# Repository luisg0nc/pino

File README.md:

<h1 align="center">pino</h1>

<p align="center">
  A desktop workbench for making circuit boards with an AI coding agent.<br>
  You point at the board. The agent writes the board in Python. pino builds it every time you save.
</p>

<p align="center">

</p>

<p align="center">
  <a href="https://pino.luisg.me/">pino.luisg.me</a> ·
  <a href="#getting-started">Getting started</a> ·
  <a href="#how-it-works">How it works</a> ·
  <a href="kernel/README.md">The engine</a> ·
  <a href="#contributing">Contributing</a>
</p>

> [!NOTE]
> pino is new and early. It is developed on Linux (Arch, Wayland), 100% using Claude Code, and runs on Linux only.
> Expect rough edges, and please [open an issue](https://github.com/luisg0nc/pino/issues) when you find one. Before
> you order a board, check every part in JLC's placement preview.

## Why pino

Coding agents can write a circuit board as code. Two things get in the way. The agent can't see the board it made,
and it's hard for you to tell it *which* track is wrong, or where a part should go. Pointing at a board is easy in
real life and slow to put into words.

pino fixes both. It runs [Claude Code](https://docs.anthropic.com/en/docs/claude-code) next to a live view of the
board, its schematic and a 3D model. You point at a part, draw an arrow to where it should go or sketch the way a
track should run, and the agent gets exactly what you pointed at: the part's reference, the pad, the net, your note.
The agent also gets tools to look at the board, measure it, read the checks and route it, so it can check its own
work before it hands it back.

pino is not a PCB editor. You don't place parts or draw tracks by hand. The board is a Python file, `board.py`, and
pino builds it into a KiCad 10 project and shows it. pino is a sibling of
[torno](https://github.com/luisg0nc/torno), the same kind of workbench for CAD parts, and shares much of its code.

## Features

- **Live builds.** Every save of `board.py` builds the schematic and the board as a KiCad 10 project and runs KiCad's
  electrical and design rule checks and pino's own. The files are the same bytes every time for the same input.
- **Point, don't describe.** Point, draw an arrow (move this here), a stroke (route this way) or a region (keep this
  clear, or put these here), each with a note. The agent gets your marks with your next message as exact references,
  never as vague words.
- **Three views.** The Schematic is KiCad's sheet, redrawn. The Board shows the layers as a technical drawing, with
  net colours as a switch. 3D is a live model of the board, parts and all, or a bare board. A part you select stays
  selected across the three.
- **The agent sees what you see.** The agent gets MCP tools of its own: `look` (a picture of a view, marks
  included), `measure`, `check`, `nets`, `trace`, `ratsnest`, `diff` between builds, `parts`, `point` to mark the
  board back at you, and the routing tools.
- **Routing in the background.** [KiCadRoutingTools](https://github.com/drandyhaas/KiCadRoutingTools) routes the
  board while you work, then the design rule check runs again. What the router leaves, the agent finishes with
  `route_net`, `nudge` and `keep`.
- **Parts you can order.** Name a part by its LCSC number and pino looks it up on
  [jlcsearch](https://github.com/tscircuit/jlcsearch): stock, price, and whether JLC calls it basic or extended. An
  extended part says why in `board.py`.
- **Fab files.** `release` writes Gerbers, drill files, a BOM and a placement file in JLC's columns, with a README
  that says what to upload and what to check in JLC's preview. Each release is a version, `fab/v1.0.0/`.
- **Every build kept.** A bar under the views groups the builds by what made them: a prompt, your own saves, a
  route. Open it with Ctrl+Shift+H to see a picture of each build, and press one to see it in the views.
- **What it cost.** Each turn ends with what Claude Code says it cost and how many tokens it took, and a turn far
  above the project's usual one says what happened in it. The Usage tab adds it up by day, conversation and prompt.
- **Local.** pino itself uploads nothing. The only requests it makes are part lookups on jlcsearch, which carry pino's
  version and nothing about you. The agent is your own `claude`, under your own login, and pino leaves its settings
  alone. In your folders, pino writes only under `<project>/.pino/` and, when you release, `<project>/fab/`.

## What goes well, and what does not

pino is made for two and four layer boards of up to about a hundred parts, made at JLC. On the reference board, an
ESP32-C6 on USB-C power with 21 parts, the router routes all 14 nets and the design rule check comes back clean in
about 20 seconds. On a dense four layer board (Watchy, a 50-net watch) it routes 45 of 50 nets, and the agent has to
finish the rest.

It needs more from you for a board that must fit an enclosure you can only measure roughly, and for radio and
high-speed layout. pino routes a USB pair as a pair and keeps a module's antenna area clear, but it checks no
impedance. Whatever the board, give the agent part numbers, sizes from the datasheet and a mark on the board in place
of a description.

## How it works

A **project** is a folder with a `board.py` in it, next to an outline of the board:

```
blinky/
├── board.py
└── outline.json
```

`board.py` names the parts, wires them into nets, and says roughly where they go:

```python
from pino import Board

b = Board("blinky", layers=2, outline="outline.json")

mcu = b.block("mcu", "MCU")
u1 = mcu.path("U1", "RF_Module:ESP32-C6-MINI-1", lcsc="C5736265", why="the ESP32-C6 module, with 4 MB of flash")
c1 = mcu.shunt("C1", "Device:C", "100nF", footprint="Capacitor_SMD:C_0402_1005Metric", lcsc="C1525")
r1 = mcu.path("R1", "Device:R", "1k", footprint="Resistor_SMD:R_0402_1005Metric", lcsc="C11702")
d1 = mcu.shunt("D1", "Device:LED", "green", footprint="LED_SMD:LED_0603_1608Metric", lcsc="C72043",
               why="a green 0603 LED; there is no basic one")

b.supply("+3V3", u1["3V3"], c1[1], external=True)
b.net("LED", u1["IO8"], r1[1])
b.net("LED_A", r1[2], d1["A"])
b.gnd(u1["GND"], c1[2], d1["K"], external=True)
b.nc_rest(u1)

b.place(u1, edge="top", center=True)
b.zone("GND", layer="B.Cu")
```

Symbols, footprints and 3D models come from KiCad's own libraries. pino writes the KiCad files itself, so the same
`board.py` always gives the same files. Positions are in millimetres from the middle of the outline, with y up.

The app is Electron. The engine is a Python package (`kernel/`) that runs `board.py`, writes the KiCad project, runs
kicad-cli for the checks and the views, and routes in the background. Each project gets its own Claude Code session,
in the project's folder, connected to pino's MCP server on `127.0.0.1`. The [engine's README](kernel/README.md) has
the full rules: the build, routing, parts, fab files and design rules.

## Getting started

### Requirements

- Linux
- Node.js 22.12 or later, and pnpm 10, to run from source
- [uv](https://docs.astral.sh/uv/), which runs the engine on Python 3.12 or later
- [KiCad 10](https://www.kicad.org/), with its symbol, footprint and 3D model libraries
- [Claude Code](https://docs.anthropic.com/en/docs/claude-code) (`claude`) on your `PATH`, logged in

pino checks all of this on its first screen and says what's missing. The first route installs the router into a
cache in your home folder, once.

### Install

The [latest release](https://github.com/luisg0nc/pino/releases/latest) has an AppImage and a `.tar.gz`, for x86-64.
They carry the app and the engine, so you don't need Node.js or pnpm. You still need uv, KiCad 10 and Claude Code.

```sh
chmod +x pino-0.1.0.AppImage
./pino-0.1.0.AppImage

# or
tar xzf pino-app-0.1.0.tar.gz
./pino-app-0.1.0/pino-app
```

On Ubuntu 23.10 and later, the `.tar.gz` stops with "The SUID sandbox helper binary was found, but is not
configured correctly". Give the helper in the extracted folder what it asks for, once:

```sh
sudo chown root:root pino-app-0.1.0/chrome-sandbox
sudo chmod 4755 pino-app-0.1.0/chrome-sandbox
```

The AppImage needs FUSE 2 (`fuse2` on Arch, `libfuse2` or `libfuse2t64` on Debian and Ubuntu). The first start
needs the network, so that uv can set up the engine's Python environment in `~/.config/pino/kernel-env`. Neither
download adds pino to your applications menu, and neither updates itself.

To run from source instead:

```sh
git clone https://github.com/luisg0nc/pino.git
cd pino
pnpm install
```

### Run from source

```sh
scripts/pino ~/boards           # open a folder of boards
scripts/pino ~/boards/blinky    # open one board in it
scripts/pino                    # what you had open last, or the first screen
```

pino keeps your boards in one folder, each board in a subfolder of its own. On the first run it offers `~/boards`.

The launcher builds the app on the first run, which also downloads Electron, and builds again when the sources
change, so `git pull` and run it again. `scripts/pino --install-desktop` adds pino to your applications menu, and
`--uninstall-desktop` removes it.

If a folder brings Claude Code settings of its own, pino asks before the first chat there.

### Your first five minutes

Copy [`kernel/tests/fixtures/reference/`](kernel/tests/fixtures/reference/), the reference board (it's in a clone and
in the release's source archive), into your folder of boards and open the copy. Click a part on the Board, then the
same part on the Schematic. Point at the LEDs and ask the agent to move them to the other edge. Watch it edit
`board.py`, the build that follows, and the routing. When the checks pass, press **Fab files…** in the status line to
see what a release would hold.

## Working with Claude Code in pino

A few habits that save time.

- **Point, don't describe.** Point at the part and write the note. The agent gets the reference and your words, not
  "the resistor near the top".
- **Give part numbers.** Name parts by their LCSC numbers, or ask the agent to find basic parts first. A part it
  guesses may be an extended part that costs more, or one JLC can't place.
- **Say where things go before the details.** The outline, the connectors on their edges, and the big parts first.
  The router does better on a board whose parts sit in sensible places.
- **Let the router go first.** Ask the agent to finish only what the router left, and draw a stroke for any track that
  has to run a certain way.
- **Release from a clean build.** pino refuses a release with failing checks or an unrouted net. Read the release's
  README, then check every part's position and rotation in JLC's preview before you pay.

## Documentation

- **[The engine](kernel/README.md)**: how to run it, the serve protocol, routing, parts, fab files, design rules
  and the build folder.
- **[The design](docs/superpowers/specs/2026-11-26-pino-design.md)**: why pino is built the way it is, and the
  [design picks](docs/superpowers/specs/2026-11-26-pino-design-picks.md) for its look.
- **[The roadmap](docs/superpowers/plans/2026-11-26-pino-roadmap.md)**: the stages and where each one stands.

## Contributing

Issues and pull requests are welcome. pino is young, so for anything bigger than a fix, please open an issue first
to talk it over. [CONTRIBUTING.md](CONTRIBUTING.md) says how, and pull requests go to `dev`.
[CLAUDE.md](CLAUDE.md) covers where things are and the rules the code holds to, with the detail by area in
`.claude/rules/`.

The tests, from the repository root:

```sh
pnpm test                               # unit tests
pnpm test:e2e                           # builds the app and drives it in a hidden window
pnpm -C app typecheck
bash .claude/hooks/guard-bash.test.sh   # needs jq and perl
env -u DISPLAY -u WAYLAND_DISPLAY uv run --directory kernel pytest   # the engine
```

No test runs the real Claude Code or reaches the network. The app's tests use a stand-in agent and a stand-in
engine, and the engine's tests use recorded jlcsearch answers.

Much of the plumbing and the look comes from torno. `shared-from-torno.json` lists each copied file, the torno commit
it came from, and whether pino changed it. `node scripts/torno-sync` reports where the two have moved apart.

## License

Copyright 2026 the pino authors.

Licensed under the [Apache License, Version 2.0](LICENSE). The engine ports some code from
[pcb-kit](https://github.com/somebox/pcb-kit) and runs KiCadRoutingTools, both under the MIT licence; see
[NOTICE](NOTICE) and [kernel/NOTICE](kernel/NOTICE).

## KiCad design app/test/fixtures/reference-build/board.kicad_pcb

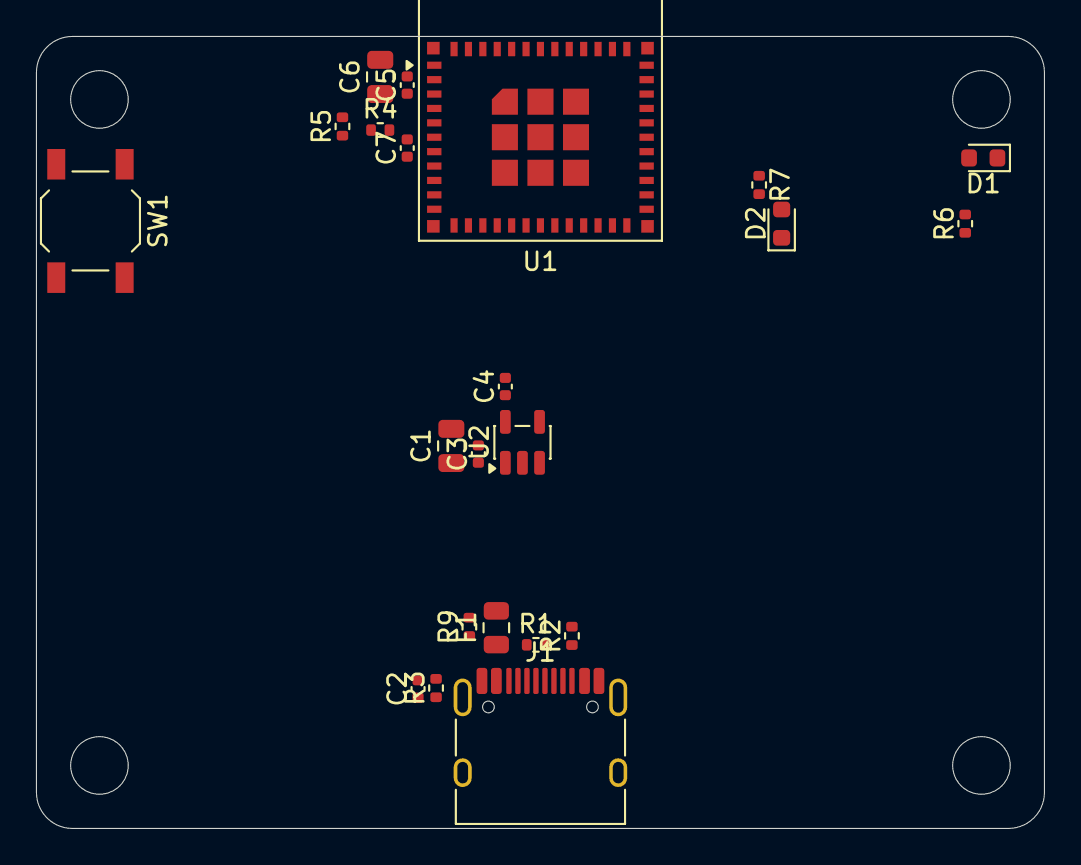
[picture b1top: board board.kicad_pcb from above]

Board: 2 copper layers, 56.0 x 44.0 mm, 26 parts (0 on the bottom side), 14 nets, no tracks yet.

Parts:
C1, C6: 10uF; C_0805_2012Metric
C2: 4.7nF; C_0402_1005Metric
C3, C4, C7: 1uF; C_0402_1005Metric
C5: 100nF; C_0402_1005Metric
D1: green; LED_0603_1608Metric
D2: red; LED_0603_1608Metric
F1: 500mA; Fuse_0805_2012Metric
H1, H2, H3, H4: MountingHole_3.2mm; MountingHole
J1: USB-C; USB_C_Receptacle_HRO_TYPE-C-31-M-12
R1, R2: 5.1k; R_0402_1005Metric
R3: 1M; R_0402_1005Metric
R4, R5: 10k; R_0402_1005Metric
R6, R7: 1k; R_0402_1005Metric
R9: 0R DNP; R_0402_1005Metric
SW1: BOOT; SW_SPST_TL3342
U1: ESP32-C6-MINI-1
U2: AP2112K-3.3; SOT-23-5

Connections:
+3V3: C4.1, C5.1, C6.1, R4.1, R5.1, R7.1, U1.3, U2.5
BOOT: R5.2, SW1.1, U1.23
CC1: J1.A5, R1.1
CC2: J1.B5, R2.1
EN: C7.1, R4.2, U1.8
GND: C1.2, C2.2, C3.2, C4.2, C5.2, C6.2, C7.2, D1.1, D2.1, J1.A1, J1.A12, J1.B1, J1.B12, R1.2, R2.2, R3.2, SW1.2, U1.1, U1.2, U1.11, U1.14, U1.36, U1.37, U1.38, U1.39, U1.40, U1.41, U1.42, U1.43, U1.44, U1.45, U1.46, U1.47, U1.48, U1.49, U1.50, U1.51, U1.52, U1.53, U2.2
LED: R6.1, U1.22
LED_A: D1.2, R6.2
PWR_LED: D2.2, R7.2
SHIELD: C2.1, J1.SH, R3.1
USB_D+: J1.A6, J1.B6, U1.18
USB_D-: J1.A7, J1.B7, U1.17
VBUS: C1.1, C3.1, F1.2, R9.2, U2.1, U2.3
VBUS_IN: F1.1, J1.A4, J1.A9, J1.B4, J1.B9, R9.1

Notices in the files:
README.md:
Apache-2.0 licence
